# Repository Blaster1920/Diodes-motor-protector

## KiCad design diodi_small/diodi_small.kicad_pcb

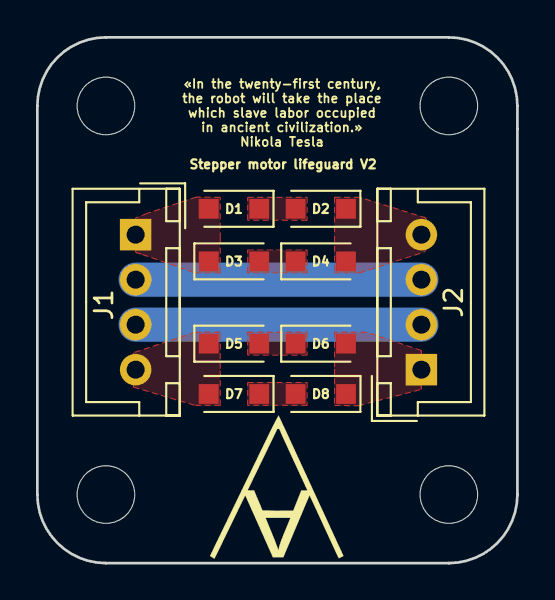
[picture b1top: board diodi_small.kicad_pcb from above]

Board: 2 copper layers, 26.7 x 29.2 mm, 12 parts (0 on the bottom side), 10 nets.

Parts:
Conn: MountingHole_3.2mm_M3
Conn#2: MountingHole_3.2mm_M3
D1, D2, D3, D4, D5, D6, D7, D8: D; D_SOD-123F
J1, J2: CONN_01X04; JST_XH_B04B-XH-A_04x2.50mm_Straight

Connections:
unnamed: D1.1, D2.2
unnamed: D1.2, D3.1, J1.1
unnamed: D2.1, D4.2, J2.4
unnamed: D3.2, D4.1
unnamed: D5.1, D7.2, J1.4
unnamed: D5.2, D6.1
unnamed: D6.2, D8.1, J2.1
unnamed: D7.1, D8.2
unnamed: J1.2, J2.3
unnamed: J1.3, J2.2

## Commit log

2018-03-08 Add files via upload
    New traces and updated labels
